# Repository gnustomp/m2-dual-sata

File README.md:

# m2-dual-sata

Schematic and PCB layout files for a adapting an M.2 slot to two SATA ports.

This is a non-standard connector suitable for use on boards like the ASRock
Rack [X470D4U][x470d4u].

This work is licensed under a
[Creative Commons Attribution-ShareAlike 4.0 International License][cc-by-sa].

[cc-by-sa]: http://creativecommons.org/licenses/by-sa/4.0/
[x470d4u]: https://www.asrockrack.com/general/productdetail.asp?Model=X470D4U#Specifications

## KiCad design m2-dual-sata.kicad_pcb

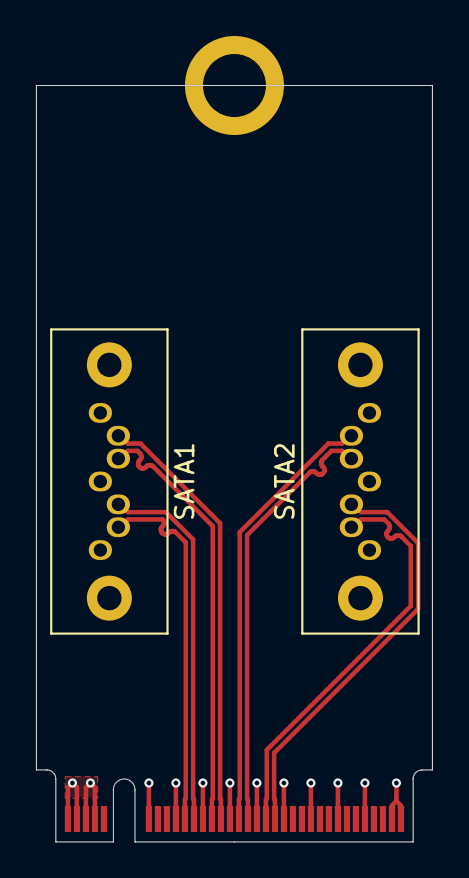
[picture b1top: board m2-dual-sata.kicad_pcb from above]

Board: 2 copper layers, 22.0 x 42.0 mm, 4 parts (0 on the bottom side), 9 nets.

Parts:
EDGE1: M.2 Key M; NGFF_M
H1: MountingHole_Pad; m2-hole
SATA1: SATA1; SATA-7_THT_VERT_1
SATA2: SATA; SATA-7_THT_VERT_1

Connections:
/SATA1_A+: EDGE1.49, SATA1.2
/SATA1_A-: EDGE1.47, SATA1.3
/SATA1_B+: EDGE1.41, SATA1.6
/SATA1_B-: EDGE1.43, SATA1.5
/SATA2_A+: EDGE1.37, SATA2.2
/SATA2_A-: EDGE1.35, SATA2.3
/SATA2_B+: EDGE1.31, SATA2.6
/SATA2_B-: EDGE1.29, SATA2.5
GND: EDGE1.1, EDGE1.3, EDGE1.9, EDGE1.15, EDGE1.21, EDGE1.27, EDGE1.33, EDGE1.39, EDGE1.45, EDGE1.51, EDGE1.57, EDGE1.69, EDGE1.71, EDGE1.73, EDGE1.75, SATA1.1, SATA1.4, SATA1.7, SATA2.1, SATA2.4, SATA2.7
